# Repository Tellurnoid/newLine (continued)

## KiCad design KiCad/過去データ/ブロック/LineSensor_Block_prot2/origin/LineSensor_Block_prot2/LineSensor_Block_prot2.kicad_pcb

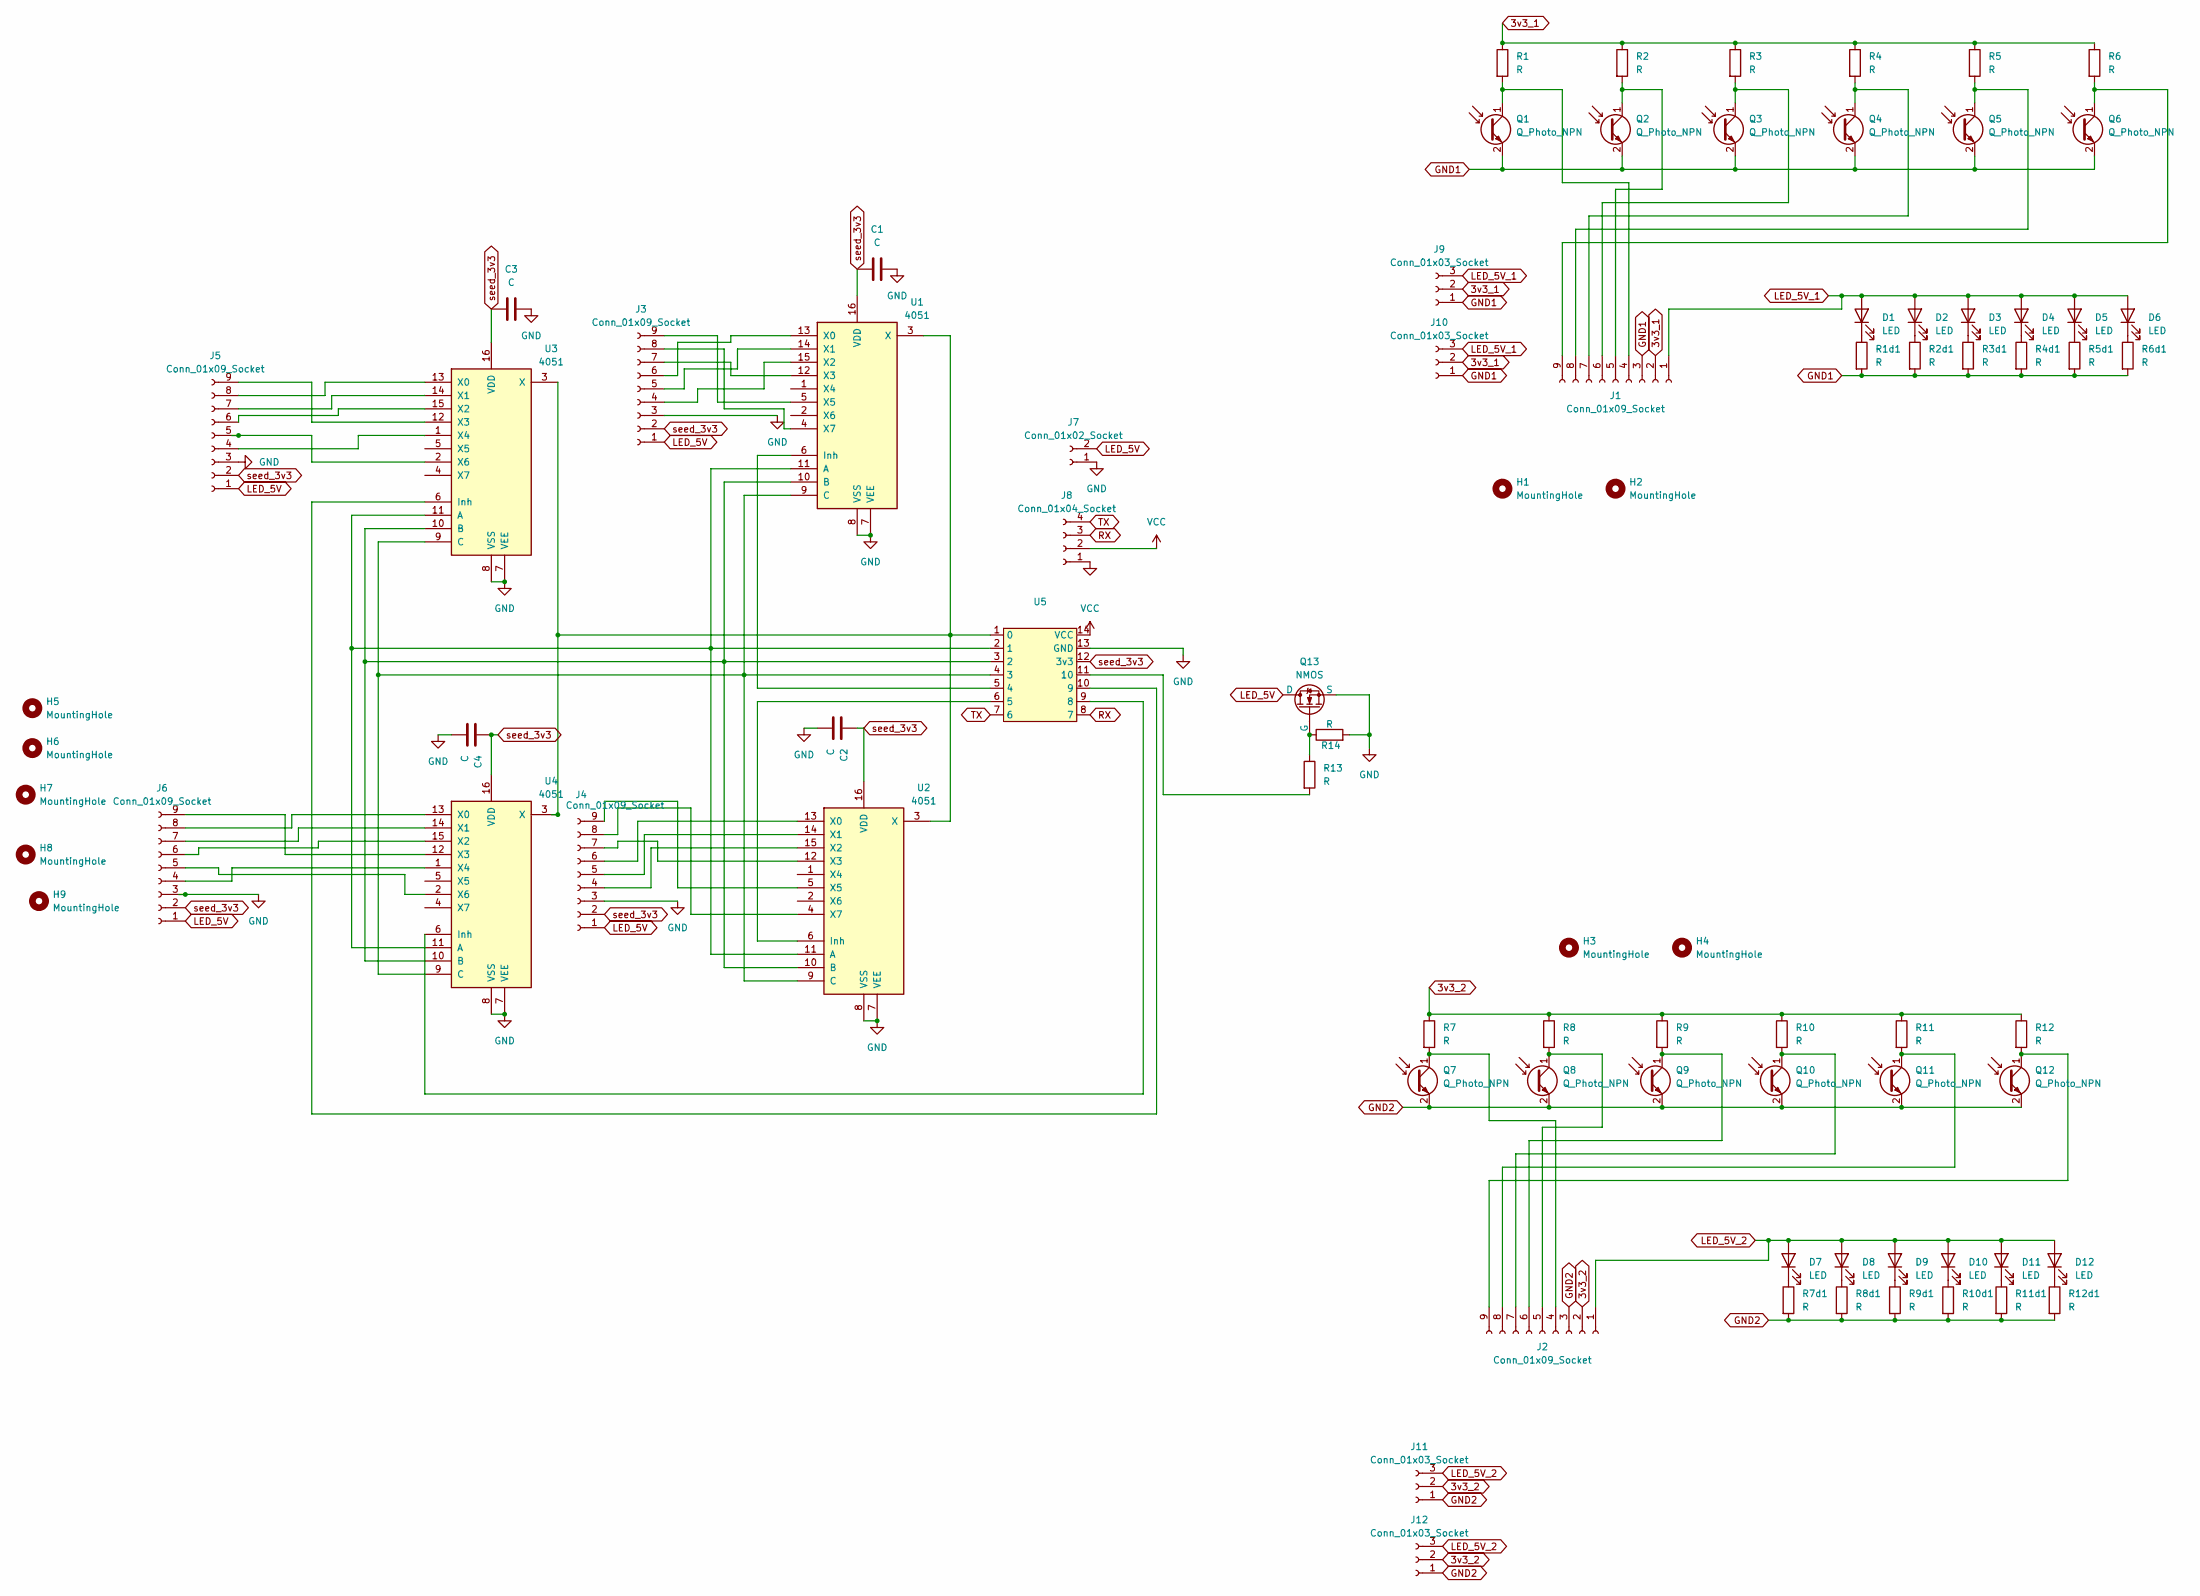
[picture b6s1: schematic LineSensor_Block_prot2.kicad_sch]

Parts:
C1, C2, C3, C4: C; C_0603_1608Metric
D1, D2, D3, D4, D5, D6, D7, D8, D9, D10, D11, D12: LED; LED_0603_1608Metric
H1, H2, H3, H4, H5, H6, H7, H8, H9: MountingHole; MountingHole_3.2mm_M3
J1, J2: Conn_01x09_Socket; PinSocket_1x09_P2.54mm_Horizontal_EDITED
J3, J4, J5, J6: Conn_01x09_Socket; PinHeader_1x09_P2.54mm_Horizontal_EDITED
J7: Conn_01x02_Socket; JST_XH_S2B-XH-A-1_1x02_P2.50mm_Horizontal
J8: Conn_01x04_Socket; JST_XH_S4B-XH-A-1_1x04_P2.50mm_Horizontal
J9, J10, J11, J12: Conn_01x03_Socket; PinHeader_1x03_P2.54mm_Vertical_EDITED
Q1, Q2, Q3, Q4, Q5, Q6, Q7, Q8, Q9, Q10, Q11, Q12: Q_Photo_NPN; LED_0603_1608Metric
Q13: NMOS; TO-251-3-1EP_Horizontal_TabDown
R1, R1d1, R2, R2d1, R3, R3d1, R4, R4d1, R5, R5d1, R6, R6d1, R7, R7d1, R8, R8d1, R9, R9d1, R10, R10d1, R11, R11d1, R12, R12d1: R; R_0603_1608Metric
R13, R14: R; R_Axial_DIN0207_L6.3mm_D2.5mm_P10.16mm_Horizontal
U1, U2, U3, U4: 4051; CERDIP-16_W7.62mm_SideBrazed_LongPads_pin_EDITED
U5: 名称未設定

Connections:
3v3_1: J1.2, J9.2, J10.2, R1.1, R2.1, R3.1, R4.1, R5.1, R6.1
3v3_2: J2.2, J11.2, J12.2, R7.1, R8.1, R9.1, R10.1, R11.1, R12.1
GND: C1.2, C2.2, C3.2, C4.2, J3.3, J4.3, J5.3, J6.3, J7.1, J8.1, Q13.3 (S), R14.2, U1.7 (VEE), U1.8 (VSS), U2.7 (VEE), U2.8 (VSS), U3.7 (VEE), U3.8 (VSS), U4.7 (VEE), U4.8 (VSS), U5.13 (GND)
GND1: J1.3, J9.1, J10.1, Q1.2 (E), Q2.2 (E), Q3.2 (E), Q4.2 (E), Q5.2 (E), Q6.2 (E), R1d1.2, R2d1.2, R3d1.2, R4d1.2, R5d1.2, R6d1.2
GND2: J2.3, J11.1, J12.1, Q7.2 (E), Q8.2 (E), Q9.2 (E), Q10.2 (E), Q11.2 (E), Q12.2 (E), R7d1.2, R8d1.2, R9d1.2, R10d1.2, R11d1.2, R12d1.2
LED_5V: J3.1, J4.1, J5.1, J6.1, J7.2, Q13.1 (D)
LED_5V_1: D1.2 (A), D2.2 (A), D3.2 (A), D4.2 (A), D5.2 (A), D6.2 (A), J1.1, J9.3, J10.3
LED_5V_2: D7.2 (A), D8.2 (A), D9.2 (A), D10.2 (A), D11.2 (A), D12.2 (A), J2.1, J11.3, J12.3
unnamed: D1.1 (K), R1d1.1
unnamed: D2.1 (K), R2d1.1
unnamed: D3.1 (K), R3d1.1
unnamed: D4.1 (K), R4d1.1
unnamed: D5.1 (K), R5d1.1
unnamed: D6.1 (K), R6d1.1
unnamed: D7.1 (K), R7d1.1
unnamed: D8.1 (K), R8d1.1
unnamed: D9.1 (K), R9d1.1
unnamed: D10.1 (K), R10d1.1
unnamed: D11.1 (K), R11d1.1
unnamed: D12.1 (K), R12d1.1
unnamed: J1.4, Q1.1 (C), R1.2
unnamed: J1.5, Q2.1 (C), R2.2
unnamed: J1.6, Q3.1 (C), R3.2
unnamed: J1.7, Q4.1 (C), R4.2
unnamed: J1.8, Q5.1 (C), R5.2
unnamed: J1.9, Q6.1 (C), R6.2
unnamed: J2.4, Q7.1 (C), R7.2
unnamed: J2.5, Q8.1 (C), R8.2
unnamed: J2.6, Q9.1 (C), R9.2
unnamed: J2.7, Q10.1 (C), R10.2
unnamed: J2.8, Q11.1 (C), R11.2
unnamed: J2.9, Q12.1 (C), R12.2
unnamed: J3.4, U1.15 (X2)
unnamed: J3.5, U1.14 (X1)
unnamed: J3.6, U1.13 (X0)
unnamed: J3.7, U1.12 (X3)
unnamed: J3.8, U1.4 (X7)
unnamed: J3.9, U1.5 (X5)
unnamed: J4.4, U2.15 (X2)
unnamed: J4.5, U2.14 (X1)
unnamed: J4.6, U2.13 (X0)
unnamed: J4.7, U2.12 (X3)
unnamed: J4.8, U2.4 (X7)
unnamed: J4.9, U2.5 (X5)
unnamed: J5.4, U3.1 (X4)
unnamed: J5.5, U3.2 (X6)
unnamed: J5.6, U3.15 (X2)
unnamed: J5.7, U3.14 (X1)
unnamed: J5.8, U3.13 (X0)
unnamed: J5.9, U3.12 (X3)
unnamed: J6.4, U4.1 (X4)
unnamed: J6.5, U4.2 (X6)
unnamed: J6.6, U4.15 (X2)
unnamed: J6.7, U4.14 (X1)
unnamed: J6.8, U4.13 (X0)
unnamed: J6.9, U4.12 (X3)
unnamed: Q13.2 (G), R13.1, R14.1
unnamed: U1.11 (A), U2.11 (A), U3.11 (A), U4.11 (A), U5.2 (1)
unnamed: U1.10 (B), U2.10 (B), U3.10 (B), U4.10 (B), U5.3 (2)
unnamed: U1.9 (C), U2.9 (C), U3.9 (C), U4.9 (C), U5.4 (3)
unnamed: U1.6 (Inh), U5.5 (4)
unnamed: U1.3 (X), U2.3 (X), U3.3 (X), U4.3 (X), U5.1 (0)
unnamed: U2.6 (Inh), U5.6 (5)
unnamed: U3.6 (Inh), U5.10 (9)
unnamed: U4.6 (Inh), U5.9 (8)
unnamed: R13.2, U5.11 (10)
RX: J8.3, U5.8 (7)
TX: J8.4, U5.7 (6)
VCC: J8.2, U5.14 (VCC)
seed_3v3: C1.1, C2.1, C3.1, C4.1, J3.2, J4.2, J5.2, J6.2, U1.16 (VDD), U2.16 (VDD), U3.16 (VDD), U4.16 (VDD), U5.12 (3v3)

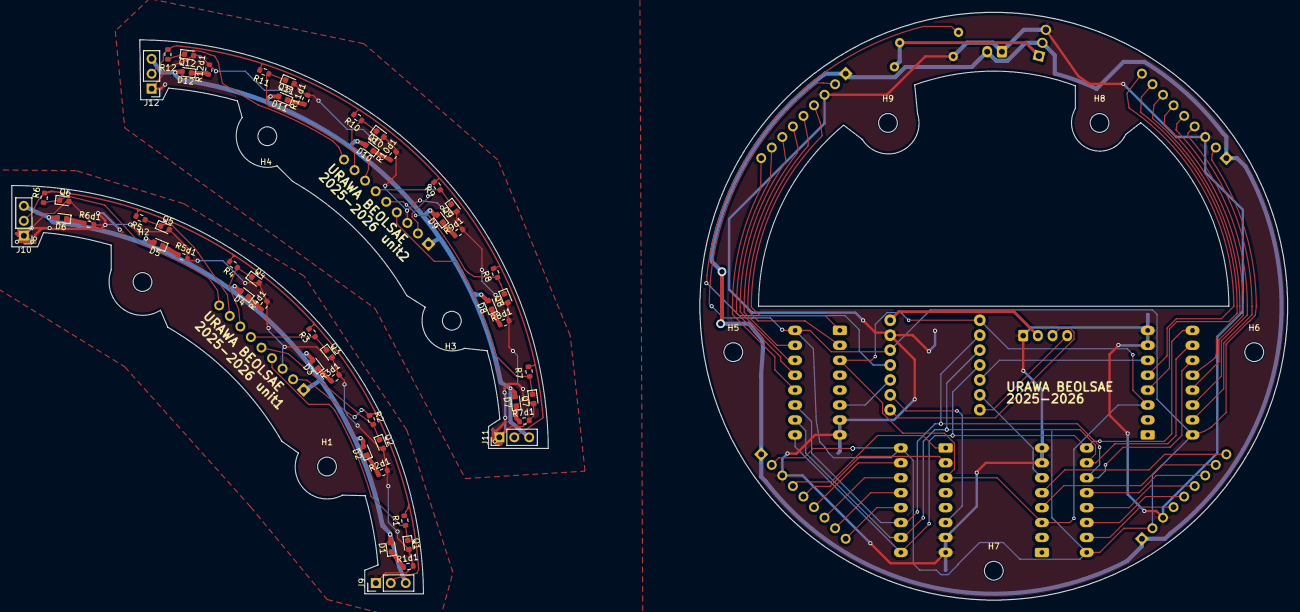
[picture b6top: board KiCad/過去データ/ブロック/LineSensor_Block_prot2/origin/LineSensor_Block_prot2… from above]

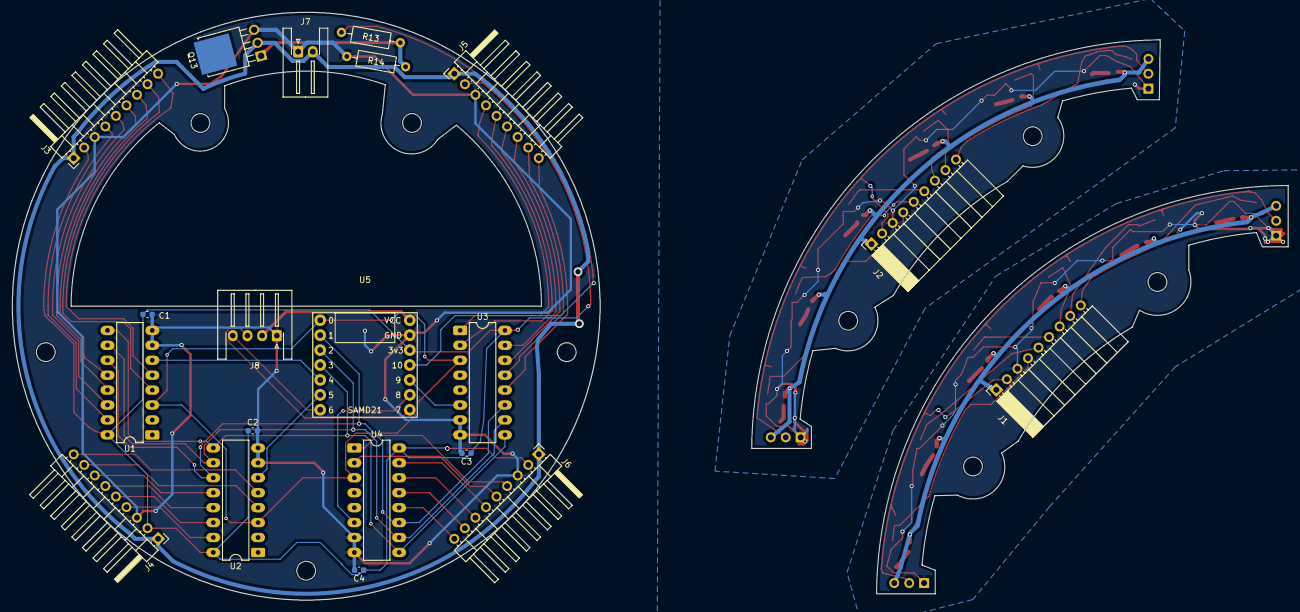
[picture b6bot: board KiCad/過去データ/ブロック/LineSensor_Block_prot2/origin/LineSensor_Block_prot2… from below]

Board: 2 copper layers, 217.0 x 100.0 mm, 81 parts (20 on the bottom side), 70 nets.

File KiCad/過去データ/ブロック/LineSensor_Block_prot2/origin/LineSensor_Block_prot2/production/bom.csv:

Designator,Footprint,Quantity,Value,LCSC Part #
"C1, C2, C3, C4",0603,4,C,
"D1, D10, D11, D12, D2, D3, D4, D5, D6, D7, D8, D9",0603,12,LED,
"J1, J2",PinSocket_1x09_P2.54mm_Horizontal_EDITED,2,Conn_01x09_Socket,
"J10, J11, J12, J9",PinHeader_1x03_P2.54mm_Vertical_EDITED,4,Conn_01x03_Socket,
"J3, J4, J5, J6",PinHeader_1x09_P2.54mm_Horizontal_EDITED,4,Conn_01x09_Socket,
J7,JST_XH_S2B-XH-A-1_1x02_P2.50mm_Horizontal,1,Conn_01x02_Socket,
J8,JST_XH_S4B-XH-A-1_1x04_P2.50mm_Horizontal,1,Conn_01x04_Socket,
"Q1, Q10, Q11, Q12, Q2, Q3, Q4, Q5, Q6, Q7, Q8, Q9",0603,12,Q_Photo_NPN,
Q13,TO-251-3-1EP_Horizontal_TabDown,1,NMOS,
"R1, R10, R10D1, R11, R11D1, R12, R12D1, R1D1, R2, R2D1, R3, R3D1, R4, R4D1, R5, R5D1, R6, R6D1, R7, R7D1, R8, R8D1, R9, R9D1",0603,24,R,
"R13, R14",R_Axial_DIN0207_L6.3mm_D2.5mm_P10.16mm_Horizontal,2,R,
"U1, U2, U3, U4",CERDIP-16_W7.62mm_SideBrazed_LongPads_pin_EDITED,4,4051,
U5,名称未設定,1,~,

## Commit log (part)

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2026-05-08 5.8授業前
2026-05-08 Remove .history from tracking
2026-05-13 ALSフットプリント作成
2026-05-27 回路図仮完成
2026-06-10 フットプイリント割当完了
2026-06-10 ネジ穴配置
